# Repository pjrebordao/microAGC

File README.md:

This is an implementation of an AGC and a DSKY coded in C on a Raspberry Pi.
One core runs the AGC emulator, the other the DSKY, both communicating through queues.
Hardware-wise, the Pi displays its contents on a touch-screen TFT. 
An SD card reader is also present (part of the TFT card) and is used for storing the "ropes" - the AGC native apps.

An AGC rope (lunlandr and lunlandr.bin) is present and contains a version of Lunar Lander coded in AGC assembler.
For this Lunar Lander version you start with an altitude of 4000 meters, -50 m/s of vertical speed and a fuel load of 500 Kg.
The game starts when you press the ENT key and can be restarted anytime by pressing the RST key on the DSKY.
You control the rate of descent by throttling up/down the LM motor. 0 for no thrust, 9 for max thrust.
If you manage to land with a vertical speed <= -3 m/s you have what it takes. Otherwise you will be rewarded with the full complement of warning lights coming on at you.

There is provision in the hardware / software to connect a simple 4-way digital joystick to control the thrust level.
Forward increases thrust, back decreases, left cuts thrust, right takes it to max.

A circuit schematic is also present in Kicad format.

Finally, credit must go to Ron Burkey who coded the entire AGC emulator in C. I merely used it as part of this game/simulation.

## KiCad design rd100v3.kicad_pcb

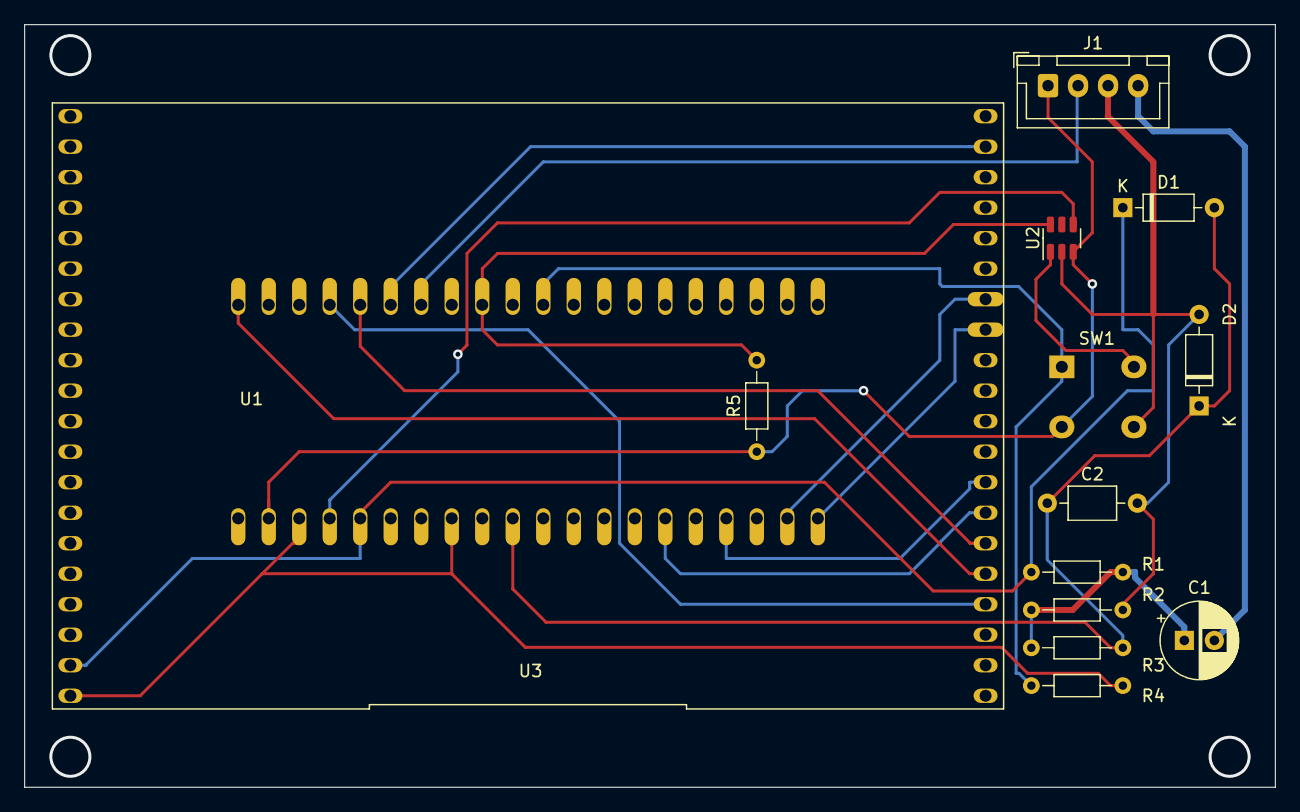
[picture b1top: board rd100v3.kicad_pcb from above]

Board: 2 copper layers, 104.1 x 63.5 mm, 14 parts (1 on the bottom side), 19 nets.

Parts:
C1: 10uF; CP_Radial_D6.3mm_P2.50mm
C2: 1nF; C_Axial_L3.8mm_D2.6mm_P7.50mm_Horizontal
D1, D2: BAT42; D_DO-35_SOD27_P7.62mm_Horizontal
J1: AnaBoard; JST_XH_B4B-XH-A_1x04_P2.50mm_Vertical
R1, R2: 100K; R_Axial_DIN0204_L3.6mm_D1.6mm_P7.62mm_Horizontal
R3: 330R; R_Axial_DIN0204_L3.6mm_D1.6mm_P7.62mm_Horizontal
R4: 10K; R_Axial_DIN0204_L3.6mm_D1.6mm_P7.62mm_Horizontal
R5: 1K; R_Axial_DIN0204_L3.6mm_D1.6mm_P7.62mm_Horizontal
SW1: SW_ONOFF; C&K PVA1
U2: MAX16150AUT+T; SOT-23-6
U3: ADA_2_8_TFT
U4: Pico; DIP-40_W17.78mm_Socket_LongPads

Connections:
unnamed: C1.1, R1.2, R2.1, R3.1
unnamed: C2.1, D1.2 (A), D2.1 (K), R3.2, U4.31 (GPIO26_ADC0)
unnamed: D1.1 (K), R1.1, U3.39 (VIN), U4.36 (3V3)
unnamed: R4.2, U3.40 (GND), U4.33 (AGND), U4.38 (GND)
unnamed: SW1.2, U2.3 (VCC), U4.39 (VSYS)
unnamed: C2.2, D2.2 (A), R2.2, SW1.4, U2.2 (GND)
unnamed: U3.19 (CCS), U4.6 (GPIO4)
unnamed: U3.4 (CLK), U4.4 (GPIO2)
unnamed: U3.7 (CS), U4.26 (GPIO20)
unnamed: U3.8 (D/C), U4.24 (GPIO18)
unnamed: U3.5 (MISO), U4.1 (GPIO0)
unnamed: U3.6 (MOSI), U4.5 (GPIO3)
unnamed: U2.4 (OUT), U4.37 (3V3_EN)
unnamed: U2.6 (CLR), U4.9 (GPIO6)
unnamed: R4.1, SW1.1, U4.11 (GPIO8)
unnamed: U3.10 (Lite), U4.14 (GPIO10), U4.15 (GPIO11), U4.16 (GPIO12), U4.17 (GPIO13)
unnamed: U3.14 (SCL), U4.21 (GPIO16)
unnamed: U3.13 (SDA), U4.22 (GPIO17)
unnamed: SW1.3, U2.1 (PB_IN)

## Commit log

2026-03-09 Add files via upload
    C code for microAGC
    AGC4 code for LUNLANDR
2026-03-09 Kicad files
2026-03-10 Add files via upload
    AGC + ACA playing Lunar Lander

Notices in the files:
rd100v3.kicad_pcb:
SMFT(c)2024
